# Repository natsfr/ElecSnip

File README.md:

# ElecSnip
Electronic Snippet
Storing all idea/crap/piece/circuit/thought

No interest for anyone else.

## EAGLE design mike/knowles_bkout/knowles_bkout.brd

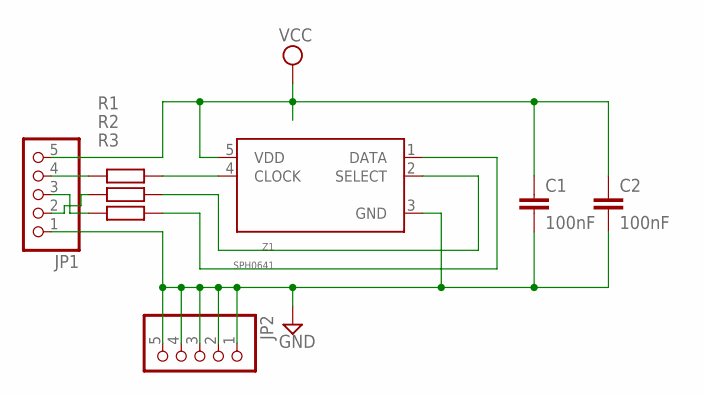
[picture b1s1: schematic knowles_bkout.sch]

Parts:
C1, C2: 100nF; C0805K
JP1, JP2: PINHD-1X5; 1X05
R1, R2, R3: R-EU_R0603; R0603
Z1: SPH0641

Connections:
GND: C1.2, C2.2, JP1.1, JP2.1, JP2.2, JP2.3, JP2.4, JP2.5, Z1.3 (GND)
unnamed: JP1.4, R1.1
unnamed: JP1.3, R3.1
unnamed: JP1.2, R2.1
unnamed: R3.2, Z1.1 (DATA)
unnamed: R2.2, Z1.2 (SELECT)
unnamed: R1.2, Z1.4 (CLOCK)
VCC: C1.1, C2.1, JP1.5, Z1.5 (VDD)

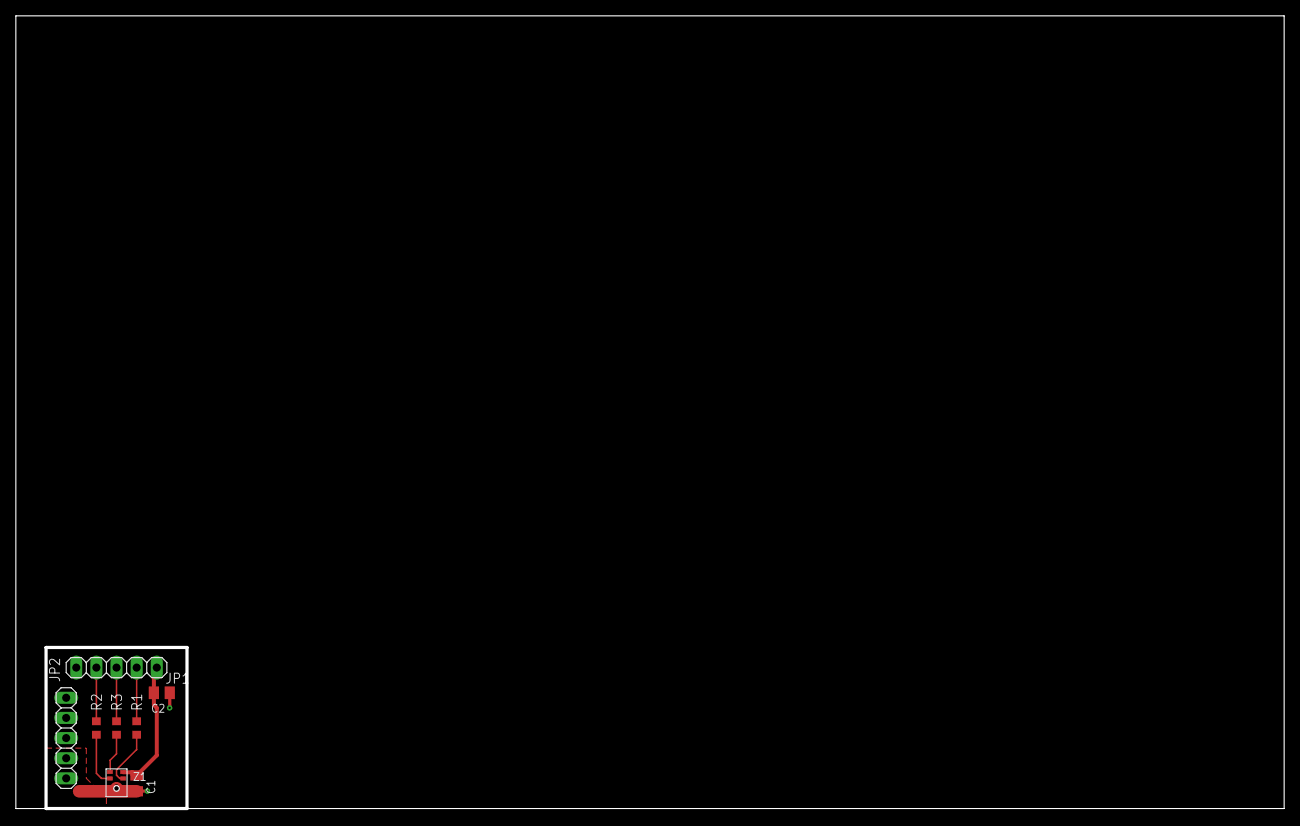
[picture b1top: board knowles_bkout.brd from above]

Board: 2 copper layers, 160.0 x 100.0 mm, 8 parts (0 on the bottom side), 8 nets.

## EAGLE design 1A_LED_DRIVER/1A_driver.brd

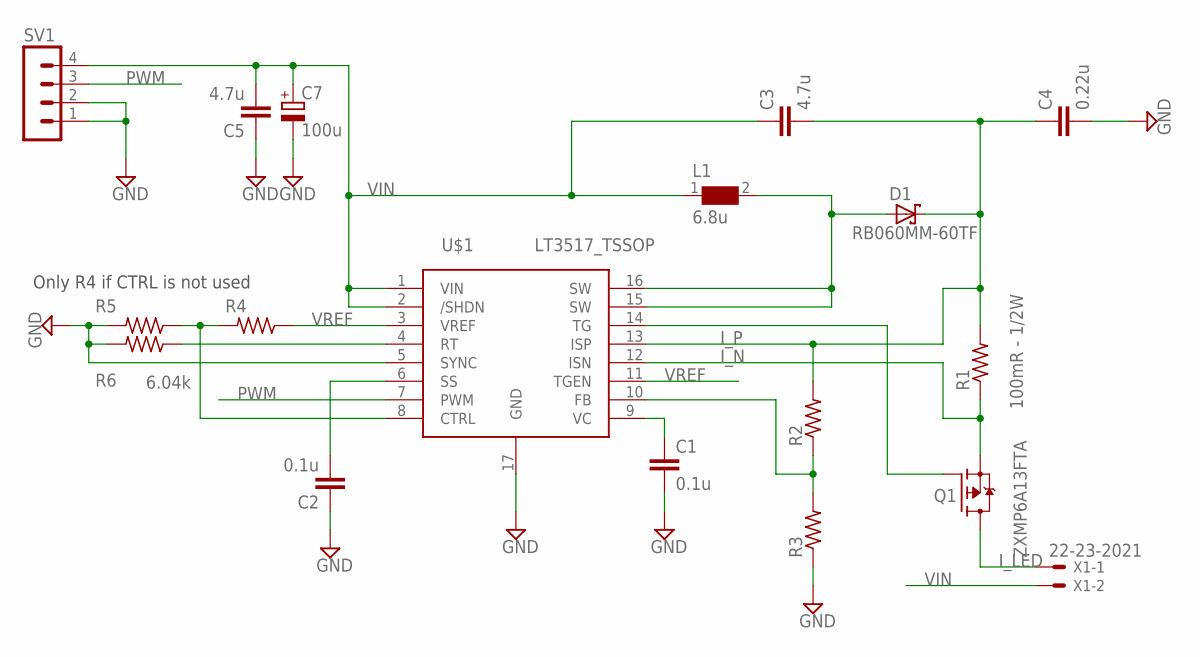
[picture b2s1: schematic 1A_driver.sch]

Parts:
C1, C2: 0.1u; R0603
C3, C5: 4.7u; R1206
C4: 0.22u; R0603
C7: 100u; E5-5
D1: RB060MM-60TF; SOD123FL
L1: 6.8u; WE-PD_1260/1245/1280/1210
Q1: ZXMP6A13FTA; SOT23
R1: 100mR - 1/2W; R1206
R2, R3, R4, R5: RES_0603; R0603
R6: 6.04k; R0603
SV1: MA04-1
U$1: LT3517_TSSOP; TSSOP16_PAD
X1: 22-23-2021

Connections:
GND: C1.2, C2.1, C4.2, C5.1, C7.-, R3.1, R5.2, R6.2, SV1.1, SV1.2, U$1.5 (SYNC), U$1.17 (GND)
I_LED: Q1.D, X1.1
I_N: Q1.S, R1.1, U$1.12 (ISN)
I_P: C3.2, C4.1, D1.C, R1.2, R2.2, U$1.13 (ISP)
unnamed: Q1.G, U$1.14 (TG)
unnamed: D1.A, L1.2, U$1.15 (SW), U$1.16 (SW)
unnamed: R2.1, R3.2, U$1.10 (FB)
unnamed: C2.2, U$1.6 (SS)
unnamed: R4.2, R5.1, U$1.8 (CTRL)
unnamed: C1.1, U$1.9 (VC)
unnamed: R6.1, U$1.4 (RT)
PWM: SV1.3, U$1.7 (PWM)
VIN: C3.1, C5.2, C7.+, L1.1, SV1.4, U$1.1 (VIN), U$1.2 (/SHDN), X1.2
VREF: R4.1, U$1.3 (VREF), U$1.11 (TGEN)

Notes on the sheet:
Only R4 if CTRL is not used

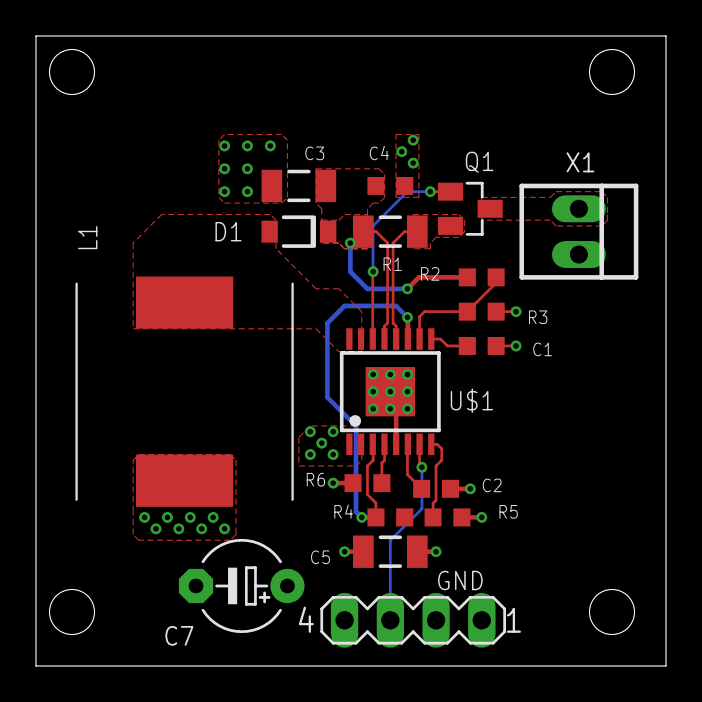
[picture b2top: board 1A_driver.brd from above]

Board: 4 copper layers, 35.0 x 35.0 mm, 18 parts (0 on the bottom side), 14 nets.

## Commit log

2015-09-06 adding ltspice modele of basic amplifier to be verified in circuit
2015-09-10 adding HIGH SPEED test
2015-09-10 changed the simple example with a SMT connector
2016-12-20 starting 1A led driver
2016-12-20 making new mosfet lib
2016-12-20 schematic finished
2016-12-24 need to finish layout for the 1A regulator
2017-01-02 almost finished led drvier
2017-01-02 finished driver, need to order stencil
2017-02-20 starting tester for metastability
2017-02-21 added hierarchical pin
2017-02-22 Adding OPAMP
2017-02-23 starting layout
2017-02-23 reversed CTS/RTS
2017-02-24 adding jtag connector
2017-02-24 starting placing components
2017-02-25 working on pcb
2017-02-25 starting simulation for sampling head + layout for clock board
2017-02-26 pcb'
2017-02-26 blabla
2017-02-27 working on layout
2017-02-27 almost finished pcb
2017-02-28 finished pcb
2017-02-28 save before generating gerber
2017-03-01 valid gerber
2017-03-05 modified bridge for demo
2017-03-13 adding automatcher script for bjt amplifier
2017-03-13 Added mutekh project for the meta tester
2017-03-14 adding python calculator
2017-03-14 removing huge simulations files
2017-03-14 adding si5338 doc and bat15 model
2017-03-15 added register map
2017-03-15 trying to startup PLL
2017-03-19 adding SCM calculation
2017-03-22 need to fix gain calculation, there are weird shit
2017-03-22 working phase shifting function
2017-03-22 merge
2017-03-22 weird git problem
2017-03-22 cleaned conflict crap
2017-03-22 changed log to log10
2017-03-23 working SCM and basic gain calculation
2017-03-24 Adding line to ignore noise parameter from infineon file
2017-03-24 matching the BFP420 amplifier
2017-03-25 changed text and verified error in book
2017-03-26 need to fix ref2z function
2017-03-26 working ref2z
2017-04-09 added step counter
2017-04-09 working eye diagram python script
2017-04-10 Added utils functions for impedance calculation
2017-07-17 devboard for knowles mic
2017-07-18 added leo footprint
2018-03-19 begins of labclock
2018-03-19 fixed stuff
